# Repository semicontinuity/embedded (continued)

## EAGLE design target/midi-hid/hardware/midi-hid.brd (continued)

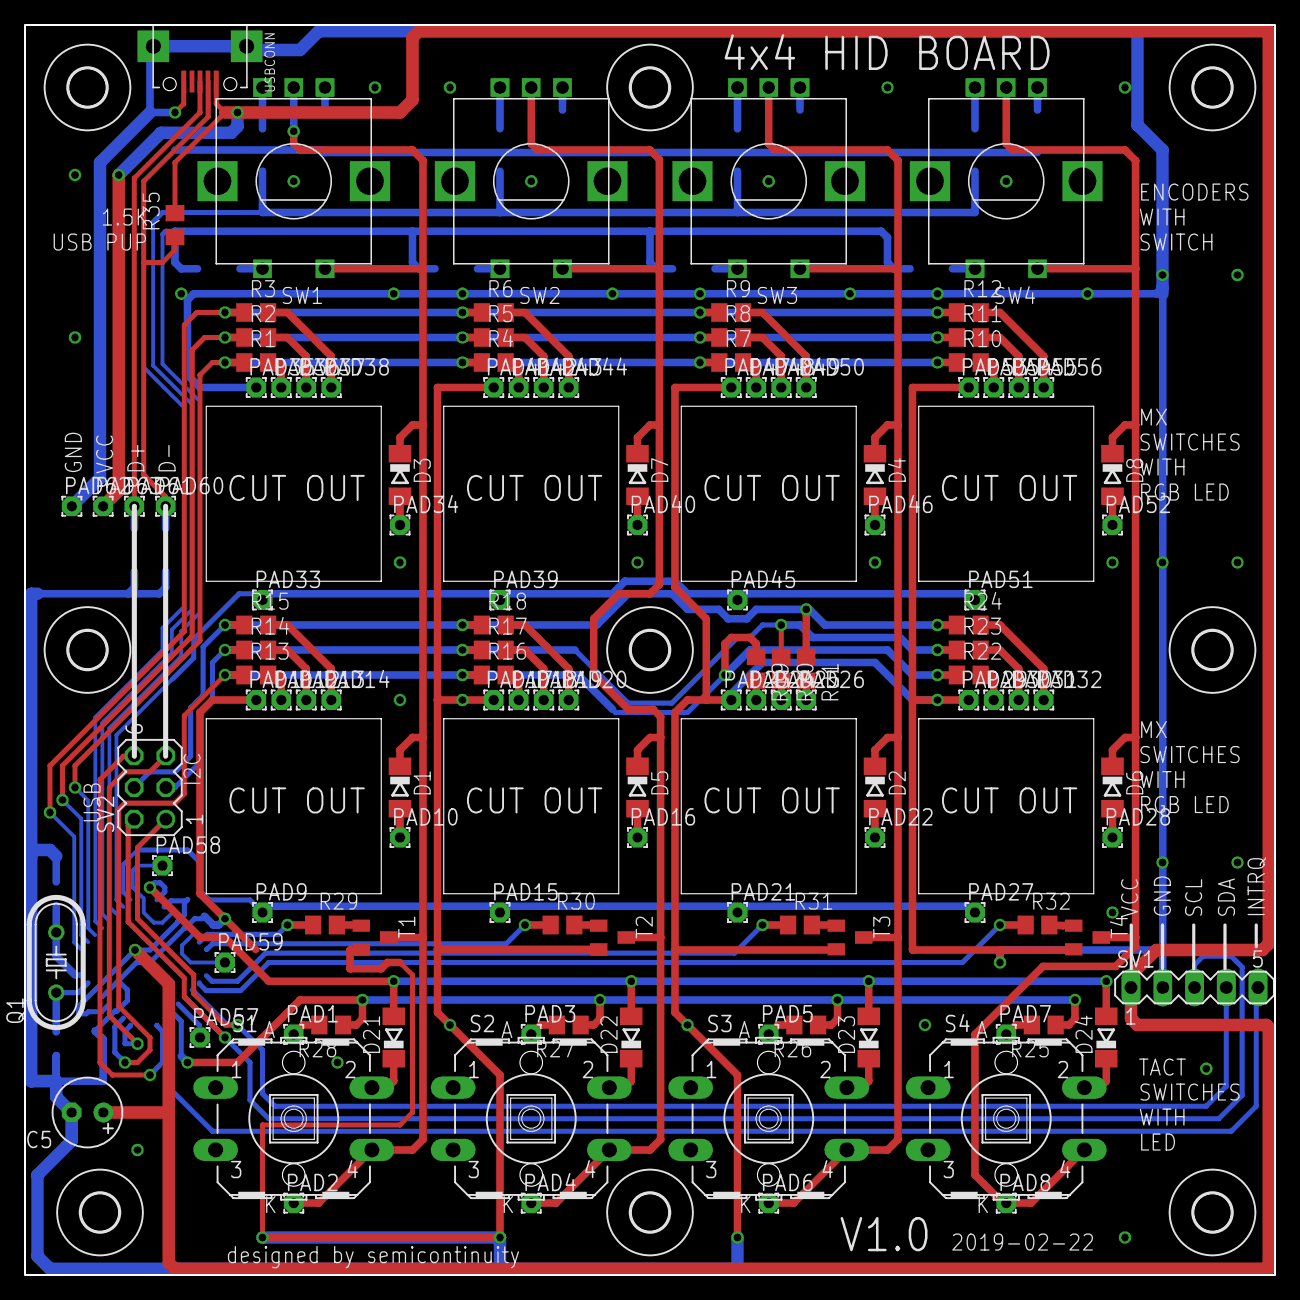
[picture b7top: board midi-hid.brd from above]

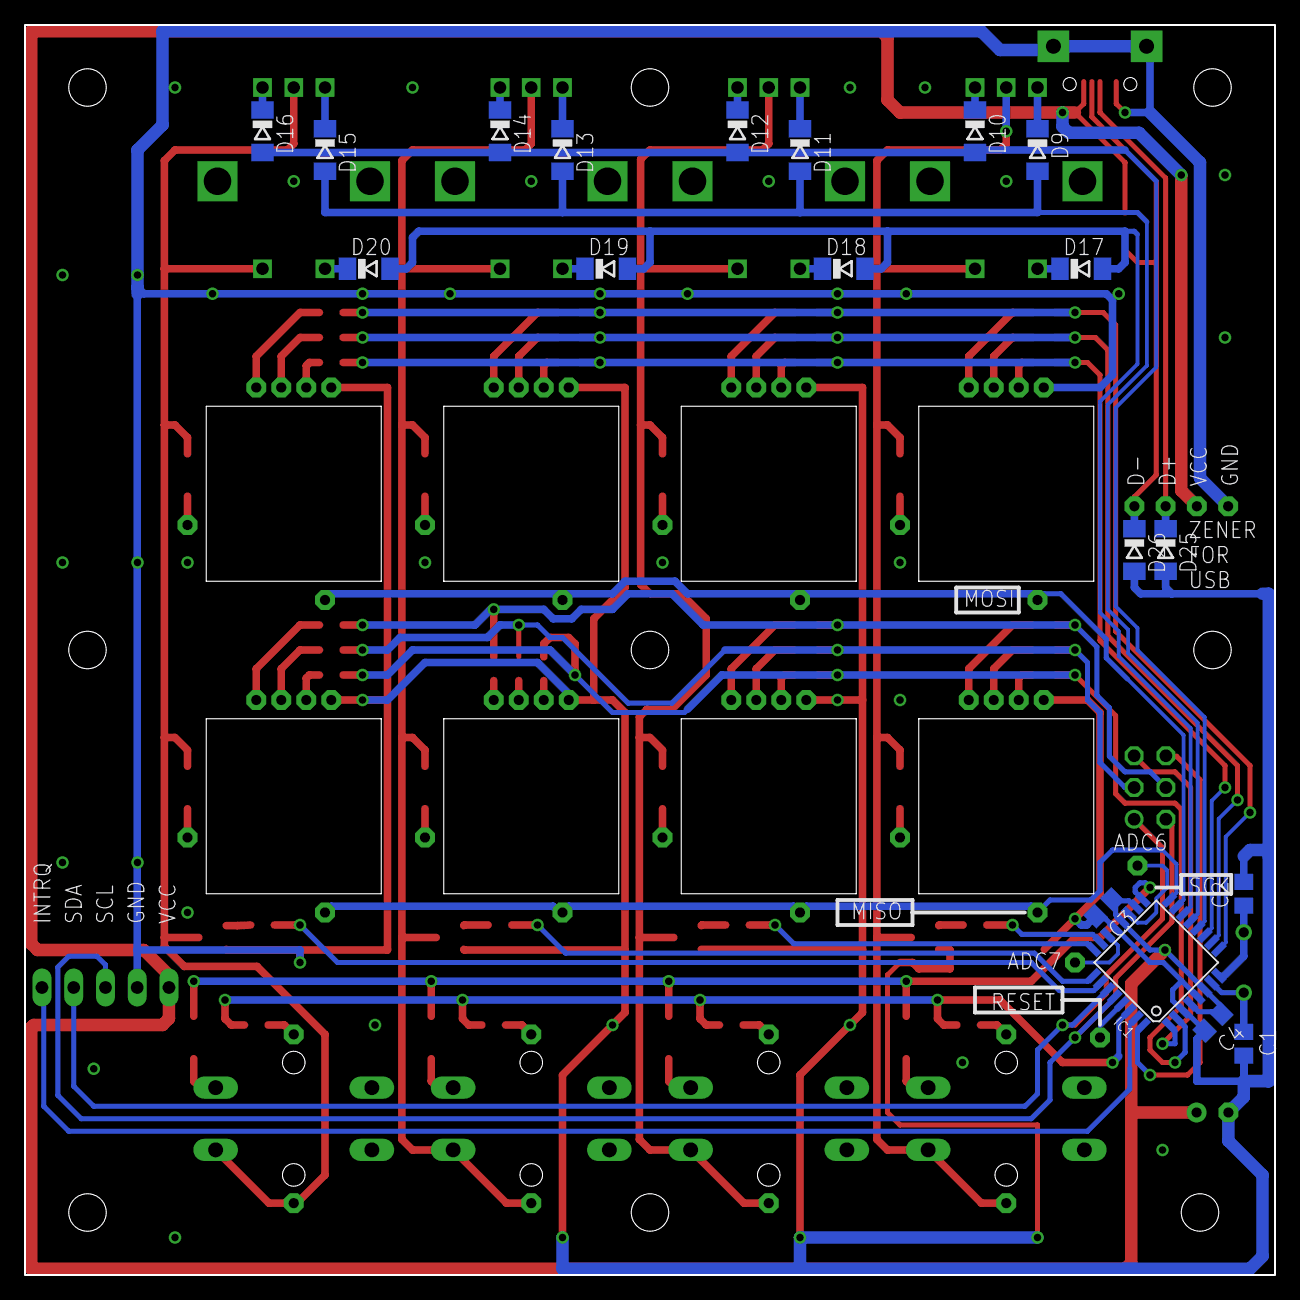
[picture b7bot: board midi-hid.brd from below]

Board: 2 copper layers, 100.0 x 100.0 mm, 153 parts (19 on the bottom side), 91 nets.

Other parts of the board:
D25, D26: SOD80C
PAD60, PAD61, PAD62, PAD63: 1,6/0,8
R35: 1.5k; R0805
SV2: MA03-2
U$1, U$2, U$3, U$4, U$5, U$6, U$7, U$8, U$9: 3,0

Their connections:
DM: D26.C, PAD60.1, R35.1; also elsewhere on the board
DP: D25.C, PAD61.1; also elsewhere on the board
GND: D25.A, D26.A, PAD62.1; also elsewhere on the board
SCL: SV2.2; also elsewhere on the board
SDA: SV2.1; also elsewhere on the board
VCC: PAD63.1, R35.2; also elsewhere on the board
